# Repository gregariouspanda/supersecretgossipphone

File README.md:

# Super Secret Gossip Phone

An ESP32 audio recorder and player. It records from a microphone to MP3 files on a microSD card, then plays them back through a small speaker. It is built for an Adafruit Feather ESP32-S3 and is written for the Arduino IDE.

> Status: the code has not been compiled or tested on hardware. Pin numbers and library header paths may need small tweaks.

## Parts list

| Item | Notes |
|---|---|
| Adafruit Feather ESP32-S3 | Any ESP32-S3 or ESP32 Feather with enough speed for software MP3 encoding. A SAMD (M0/M4) Feather is too slow. |
| microSD card breakout (3V-compatible) | Plus a microSD card, 32 GB or smaller, formatted FAT32. |
| I2S MEMS microphone breakout | SPH0645, ICS-43434, or INMP441. |
| I2S amplifier breakout | MAX98357A (3 W class-D). |
| Speaker | 4 to 8 ohm, around 3 W. |
| Rotary phone dial | An old telephone dial with a pulse contact (two wires). Dialing a digit opens the contact that many times (ten pulses for 0). |
| 20x4 I2C character LCD (HD44780 with PCF8574 backpack) | Shows the file list, the selected recording and record status. Default I2C address 0x27 (some are 0x3F). |
| On/on SPDT toggle switch | Switches between RECORD and LISTEN mode. |
| 1 external LED (any color, 3 or 5 mm) and a 330 ohm resistor | Recording indicator. The carrier board has the resistor and a 2-pin header, so the LED can sit on your enclosure on short wires. |
| LiPo battery, 3.7 V (optional) | Plugs into the Feather's JST connector for portable use. |
| Breadboard and jumper wires, or a perfboard | Header pins for the Feather and breakouts. |

## Wiring

The microphone and amplifier share the I2S clock lines (BCLK and WS) and use separate data pins. All pins are defined at the top of `mp3_recorder.ino`.

### microSD breakout

| SD breakout | Feather |
|---|---|
| 3V / VCC | 3V |
| GND | GND |
| CLK | SCK |
| DI / MOSI | MOSI |
| DO / MISO | MISO |
| CS | D10 |

### I2S microphone

| Mic | Feather |
|---|---|
| 3V / VDD | 3V |
| GND | GND |
| BCLK | D9 |
| LRCL / WS | D6 |
| DOUT | D12 |
| SEL / L/R | GND (left channel; match the code if you change it) |

### I2S amplifier (MAX98357A)

| Amp | Feather |
|---|---|
| VIN | USB (5 V) for more volume, or 3V |
| GND | GND |
| BCLK | D9 |
| LRC | D6 |
| DIN | D5 |
| Speaker +/- | Speaker |

### Rotary phone dial

Use the pulse contact, the pair of wires that opens and closes as the dial returns home. Which wires those are depends on the phone, so test with a continuity meter: the pair that is closed at rest and clicks open and closed while the dial spins back. The other contacts (the off-normal switch, the hook switch and the bell) are not used.

| Dial | Feather |
|---|---|
| Pulse contact, one wire | A3 |
| Pulse contact, other wire | GND |

### Recording LED

| LED | Feather |
|---|---|
| Anode (+, long leg) through a 330 ohm resistor | D11 |
| Cathode (-, short leg) | GND |

The LED is external and uses D11, so the Feather's own D13 LED stays unused.

### LCD (I2C)

| LCD backpack | Feather |
|---|---|
| GND | GND |
| VCC | USB (5 V) |
| SDA | SDA |
| SCL | SCL |

> Most PCF8574 backpacks pull SDA and SCL up to their own supply. With the LCD on 5 V that puts 5 V on the ESP32's 3.3 V pins. Cut or remove the backpack's pull-up resistors (the Feather already has I2C pull-ups to 3.3 V), or use a 3.3 V LCD.

### Mode toggle (on/on SPDT)

| Toggle | Feather |
|---|---|
| Common (middle) | D13 |
| One throw (LISTEN) | GND |
| Other throw (RECORD) | 3V |

## Software setup

1. Install the Arduino IDE and the **esp32 by Espressif** board package. Select the Adafruit Feather ESP32-S3 board.
2. Install these three libraries from pschatzmann (Library Manager or GitHub):
   - `arduino-audio-tools`
   - `arduino-libshine` (MP3 encoder)
   - `arduino-libhelix` (MP3 decoder)
   - Also install **LiquidCrystal I2C** (Frank de Brabander) for the LCD.
3. Open `mp3_recorder/mp3_recorder.ino`, then compile and upload.
4. Open the Serial Monitor at 115200 baud to see status messages.

## Usage

Flip the **mode toggle** to RECORD or LISTEN, then use the dial.

**RECORD mode**

| Dial | What it does |
|---|---|
| 9 | Record. Dial 9 again to stop. Recording also stops by itself after 5 minutes. Files are saved as `REC001.mp3`, `REC002.mp3`, and so on. |
| 8 | Keep. Locks in the recording you just made so it can no longer be replaced. |
| 5 | Delete and re-record. Within 1 minute after a recording ends, this deletes that recording and records over it under the same name. Only the most recent recording can be replaced. |

After a recording ends the LCD shows how many seconds are left to keep or re-record it. Dialing 9 instead starts a new file and leaves the previous one as it is. After the minute is up, or after a reset or power cycle, the old recording can no longer be replaced.

**LISTEN mode:** dial the number of the recording you want. Dial 5 for `REC005.mp3`, or 1 then 2 for `REC012.mp3` (up to three digits). The LCD shows the number and file name as you dial, and it plays about 2 seconds after the last digit. Dial any digit while it plays to stop it.

Flipping the toggle while recording or playing stops it.

**Recording LED:** it is on while recording. At the 1 minute mark it goes dark for 2 seconds, then comes back on. For the last 30 seconds (4:30 to 5:00) it blinks once per second until recording stops. It is off when not recording.

## Troubleshooting

- **"SD card init failed":** check the wiring, the FAT32 format, and the CS pin.
- **Silent or noisy recordings:** check the mic's SEL pin, the 3.3 V supply, and that the I2S pins match the code.
- **No playback sound:** check the amp's wiring and speaker polarity. Power the amp from 5 V for more volume.
- **Choppy audio:** use a faster SD card, or lower `SAMPLE_RATE` in the sketch (for example, 22050).
- **Compile errors about codec headers:** library versions differ. Adjust the `#include "AudioTools/AudioCodecs/..."` lines to match the installed version.

## Circuit board

The `hardware/` folder has a KiCad 10 schematic and a 72 x 86 mm two-layer carrier board. The Feather and the three breakouts plug into sockets, and the phone dial, mode toggle, LED and LCD connect to it. See [hardware/README.md](hardware/README.md).

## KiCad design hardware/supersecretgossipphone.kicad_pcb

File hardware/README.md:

# Circuit board (KiCad 10)

A single two-layer carrier board. The Feather ESP32-S3 plugs into two female headers (J1, J2). The microSD, I2S microphone and I2S amplifier breakouts plug into sockets (J3, J4, J5). The board also carries an LED resistor and header (J6), a 4-pin LCD socket (J7), a 3-pin mode toggle header (J8), a 2-pin rotary phone dial header (J9) and a 3-pin amp power jumper (JP1). It is 72 x 86 mm, with ground planes on both layers.

| File | What it is |
|---|---|
| `supersecretgossipphone.kicad_sch` | Schematic |
| `supersecretgossipphone.kicad_pcb` | Board layout |
| `schematic.pdf`, `pcb_layout.pdf`, `pcb_top.png` | Previews |
| `fabrication_gerbers.zip` | Gerbers and drill files for a board house |

## Pin map (matches `mp3_recorder.ino`)

| Function | Feather pin |
|---|---|
| microSD chip select | D10 (SCK, MOSI, MISO for data) |
| I2S bit clock / word select | D9 / D6 |
| Microphone data in / amp data out | D12 / D5 |
| Rotary phone dial pulse contact | A3 (other wire to GND) |
| Mode toggle | D13 (3V = RECORD, GND = LISTEN) |
| LCD | SDA, SCL, and 5 V from USB |
| Recording LED (external, through R1 330 ohm) | D11 |

## Wiring notes

- **JP1** picks the amp supply: shunt pins 1-2 for USB 5 V (louder) or 2-3 for 3.3 V.
- **J6** is the external LED: pin 1 is the anode (after R1), pin 2 is ground.
- **J8** is the mode toggle: the middle pin is the common terminal; one end goes to GND (LISTEN), the other to 3V (RECORD).
- **J9** is the phone dial's pulse contact: pin 1 is the pulse wire (to A3), pin 2 is GND.
- **J7** order is GND, VCC, SDA, SCL, which is common but not universal. Check your LCD backpack.
- The microphone's SEL pin is tied to GND (left channel).

## Not yet verified

- The board has passed KiCad's design rule check (no errors, nothing unrouted) and the schematic passes ERC apart from three harmless label-name warnings. It has **not** been built or tested.
- The Feather header positions come from Adafruit's Feather specification: the 16-pin row is on the bottom edge when USB is on the left, the 12-pin row is on top, 0.8 in apart, and the two rows end at the same point so BAT sits opposite A0. Check this against your board before ordering.
- Breakout pin orders follow the Adafruit boards (microSD 254, SPH0645 and MAX98357A). Check them against the exact boards you buy.
- The dial's pulse contact polarity and timing depend on the phone. The sketch assumes the contact is closed at rest and opens once per pulse; if your dial behaves differently, the constants at the top of the sketch may need adjusting.

## Regenerating

`tools/` holds the Python scripts that generate both files from one pin list. They need KiCad 10 installed (see the top of each script).

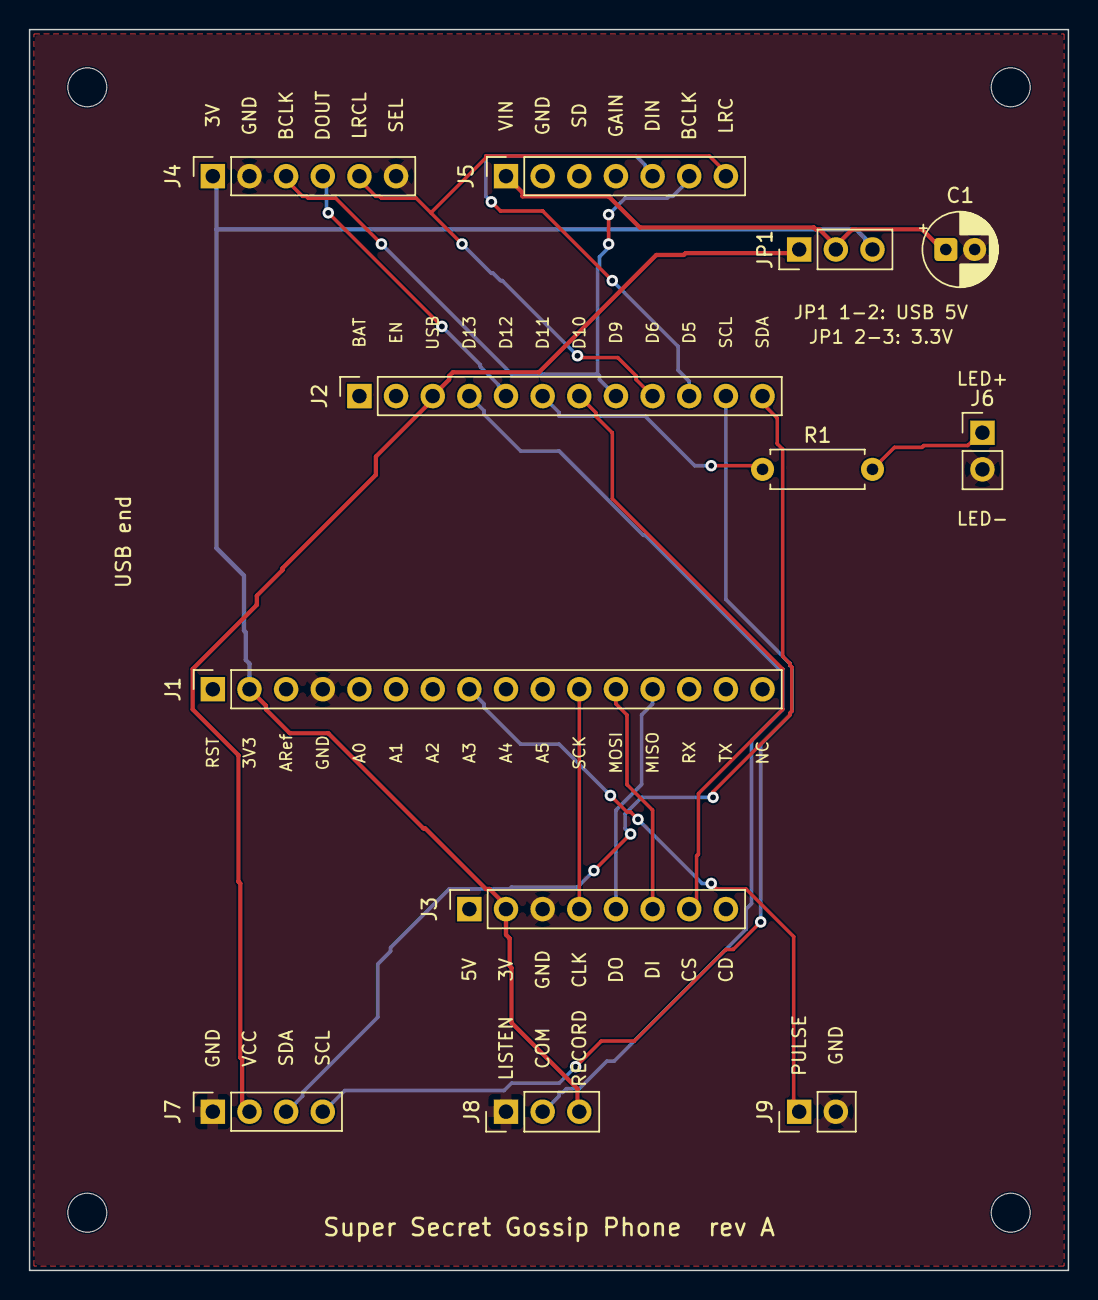
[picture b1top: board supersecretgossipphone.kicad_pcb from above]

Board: 2 copper layers, 72.0 x 86.0 mm, 16 parts (0 on the bottom side), 18 nets.

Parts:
C1: 10uF; CP_Radial_D5.0mm_P2.00mm
H1, H2, H3, H4: M2.5; MountingHole_2.7mm_M2.5
J1: Feather 16-pin; PinSocket_1x16_P2.54mm_Vertical
J2: Feather 12-pin; PinSocket_1x12_P2.54mm_Vertical
J3: microSD breakout; PinSocket_1x08_P2.54mm_Vertical
J4: I2S mic breakout; PinSocket_1x06_P2.54mm_Vertical
J5: I2S amp breakout; PinSocket_1x07_P2.54mm_Vertical
J6: External LED; PinHeader_1x02_P2.54mm_Vertical
J7: 20x4 I2C LCD; PinSocket_1x04_P2.54mm_Vertical
J8: Mode toggle; PinHeader_1x03_P2.54mm_Vertical
J9: Rotary phone dial; PinHeader_1x02_P2.54mm_Vertical
JP1: Amp power select; PinHeader_1x03_P2.54mm_Vertical
R1: 330R; R_Axial_DIN0207_L6.3mm_D2.5mm_P7.62mm_Horizontal

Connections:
+3V3: J1.2, J3.2, J4.1, J8.3, JP1.3
+5V: J2.3, J7.2, JP1.1
/AMP_VIN: C1.1, J5.1, JP1.2
/DIAL: J1.8, J9.1
/I2C_SCL: J2.11, J7.4
/I2C_SDA: J2.12, J7.3
/I2S_BCLK: J2.8, J4.3, J5.6
/I2S_MIC: J2.5, J4.4
/I2S_SPK: J2.10, J5.5
/I2S_WS: J2.9, J4.5, J5.7
/LED_A: J6.1, R1.2
/LED_DRV: J2.6, R1.1
/MODE: J2.4, J8.2
/SD_CS: J2.7, J3.7
/SD_MISO: J1.13, J3.5
/SD_MOSI: J1.12, J3.6
/SD_SCK: J1.11, J3.4
GND: C1.2, J1.4, J3.3, J4.2, J4.6, J5.2, J6.2, J7.1, J8.1, J9.2

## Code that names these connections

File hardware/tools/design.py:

"""Shared design data for the Super Secret Gossip Phone carrier board."""
# Feather ESP32-S3 header pin names, pin 1 first.
FEATHER_16 = ["RST","3V3","ARef","GND","A0","A1","A2","A3","A4","A5","SCK","MOSI","MISO","RX","TX","NC"]
FEATHER_12 = ["BAT","EN","USB","D13","D12","D11","D10","D9","D6","D5","SCL","SDA"]

# Net assigned to a Feather pin (others are unconnected).
FEATHER_NETS = {
    "3V3":"+3V3","GND":"GND","USB":"+5V",
    "A3":"DIAL","D13":"MODE","SCL":"I2C_SCL","SDA":"I2C_SDA",
    "SCK":"SD_SCK","MOSI":"SD_MOSI","MISO":"SD_MISO","D10":"SD_CS",
    "D11":"LED_DRV","D9":"I2S_BCLK","D6":"I2S_WS","D12":"I2S_MIC","D5":"I2S_SPK",
}
# Breakout headers, listed in the physical pin order of the Adafruit breakouts.
SD_PINS  = [("5V",None),("3V","+3V3"),("GND","GND"),("CLK","SD_SCK"),("DO","SD_MISO"),("DI","SD_MOSI"),("CS","SD_CS"),("CD",None)]
MIC_PINS = [("3V","+3V3"),("GND","GND"),("BCLK","I2S_BCLK"),("DOUT","I2S_MIC"),("LRCL","I2S_WS"),("SEL","GND")]
AMP_PINS = [("VIN","AMP_VIN"),("GND","GND"),("SD",None),("GAIN",None),("DIN","I2S_SPK"),("BCLK","I2S_BCLK"),("LRC","I2S_WS")]
JP_PINS  = [("5V","+5V"),("VIN","AMP_VIN"),("3V3","+3V3")]
LCD_PINS  = [("GND","GND"),("VCC","+5V"),("SDA","I2C_SDA"),("SCL","I2C_SCL")]
MODE_PINS = [("LISTEN","GND"),("COM","MODE"),("RECORD","+3V3")]
